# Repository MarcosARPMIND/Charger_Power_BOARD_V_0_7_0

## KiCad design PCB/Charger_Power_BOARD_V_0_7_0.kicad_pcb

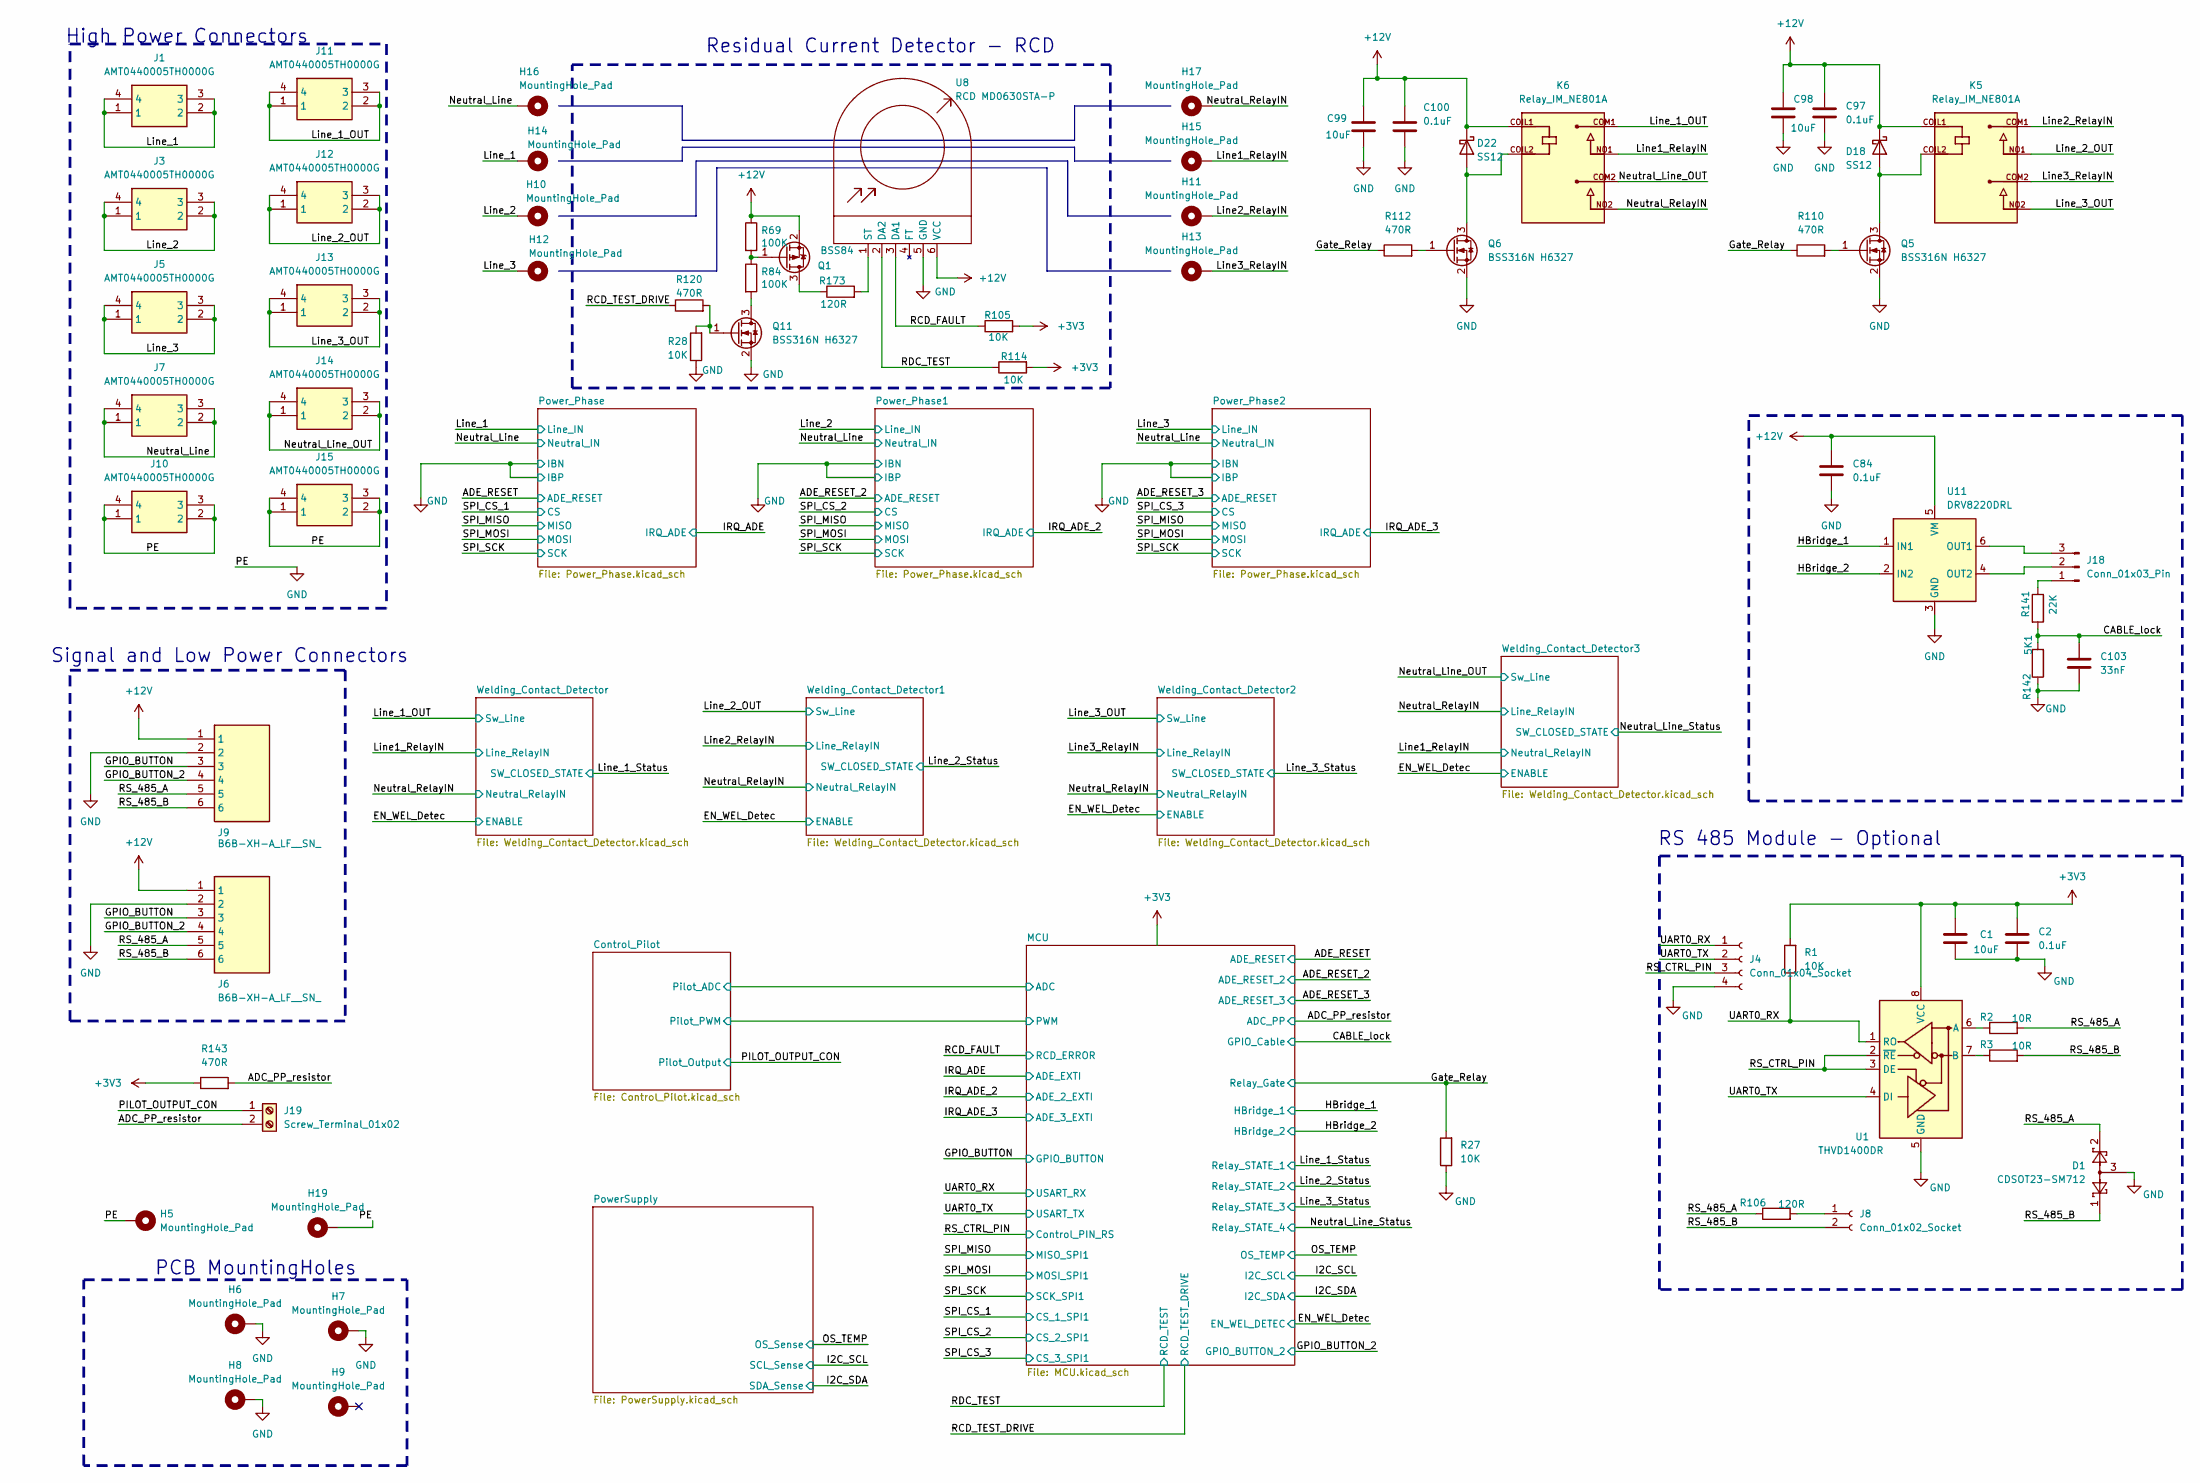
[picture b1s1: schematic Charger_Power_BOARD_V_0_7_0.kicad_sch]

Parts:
C1: 10uF; C_1206_3216Metric; MPN GMK316AB7106KL-TR
C2, C84, C97, C100: 0.1uF; C_0603_1608Metric; MPN CL10B104MB8NNNC
C98, C99: 10uF; C_1206_3216Metric
C103: 33nF; C_0603_1608Metric
D1: CDSOT23-SM712; SOT-23-3; MPN CDSOT23-SM712
D18, D22: SS12; D_SMA; MPN SS12-E3/61T
H5, H10, H11, H12, H13, H14, H15, H16, H17, H19: MountingHole_Pad; MountingHole_3.2mm_M3_DIN965_Pad_TopBottom
H6, H7, H8: MountingHole_Pad; MountingHole_5.3mm_M5_DIN965_Pad_TopBottom
H9: MountingHole_Pad; MountingHole_5.3mm_M5
J1, J3, J5, J7, J10, J11, J12, J13, J14, J15: AMT0440005TH0000G
J4: Conn_01x04_Socket; PinHeader_1x04_P2.54mm_Vertical
J6, J9: B6B-XH-A_LF__SN_; SHDR6W64P0X250_1X6_1740X575X700P
J8: Conn_01x02_Socket; PinHeader_1x02_P2.54mm_Vertical
J18: Conn_01x03_Pin; JST_VH_B3P-VH-FB-B_1x03_P3.96mm_Vertical
J19: Screw_Terminal_01x02; TerminalBlock_Phoenix_MKDS-3-2-5.08_1x02_P5.08mm_Horizontal
K5, K6: Relay_IM_NE801A
Q1: BSS84; SOT-23
Q5, Q6, Q11: BSS316N H6327; SOT-23; MPN BSS316N H6327
R1, R27, R28, R105, R114: 10K; R_0603_1608Metric; MPN RCS060310K0FKEA
R2, R3: 10R; R_0603_1608Metric; MPN 0603WAF100JT1E
R69, R84: 100K; R_0603_1608Metric
R106: 120R; R_0603_1608Metric; MPN CRCW0603120RFKEAC
R110, R112, R120, R143: 470R; R_0603_1608Metric
R141: 22K; R_0603_1608Metric
R142: 5K1; R_0603_1608Metric
R173: 120R; R_0603_1608Metric; MPN RE0603FRE07150RL
U1: THVD1400DR; SOIC127P600X175-8N
U8: RCD MD0630STA-P; RCD_MD0630STA_P
U11: DRV8220DRL; SOT-563

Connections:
+3V3: C1.2, C2.1, R1.2, R105.2, R114.2, R143.1, U1.8 (VCC); also elsewhere on the board
+12V: C84.1, C97.1, C98.1, C99.1, C100.1, D18.1 (K), D22.1 (K), J6.1, J9.1, K5.COIL1, K6.COIL1, Q1.2 (S), R69.1, U8.6 (VCC), U11.5 (VM); also elsewhere on the board
/ADC_PP_resistor: J19.2, R143.2; also elsewhere on the board
/CABLE_lock: C103.1, R141.2, R142.2; also elsewhere on the board
/GPIO_BUTTON: J6.3, J9.3; also elsewhere on the board
/GPIO_BUTTON_2: J6.4, J9.4; also elsewhere on the board
/Gate_Relay: R27.2, R110.1, R112.1; also elsewhere on the board
/HBridge_1: U11.1 (IN1); also elsewhere on the board
/HBridge_2: U11.2 (IN2); also elsewhere on the board
/Line1_RelayIN: H15.1 (1_1), K6.NO1; also elsewhere on the board
/Line2_RelayIN: H11.1 (1_1), K5.COM1; also elsewhere on the board
/Line3_RelayIN: H13.1 (1_1), K5.COM2; also elsewhere on the board
/Line_1: H14.1 (1_1), J1.1, J1.2, J1.3, J1.4; also elsewhere on the board
/Line_1_OUT: J11.1, J11.2, J11.3, J11.4, K6.COM1; also elsewhere on the board
/Line_2: H10.1 (1_1), J3.1, J3.2, J3.3, J3.4; also elsewhere on the board
/Line_2_OUT: J12.1, J12.2, J12.3, J12.4, K5.NO1; also elsewhere on the board
/Line_3: H12.1 (1_1), J5.1, J5.2, J5.3, J5.4; also elsewhere on the board
/Line_3_OUT: J13.1, J13.2, J13.3, J13.4, K5.NO2; also elsewhere on the board
/Neutral_Line: H16.1 (1_1), J7.1, J7.2, J7.3, J7.4; also elsewhere on the board
/Neutral_Line_OUT: J14.1, J14.2, J14.3, J14.4, K6.COM2; also elsewhere on the board
/Neutral_RelayIN: H17.1 (1_1), K6.NO2; also elsewhere on the board
/PILOT_OUTPUT_CON: J19.1; also elsewhere on the board
/RCD_FAULT: R105.1, U8.3 (DA1); also elsewhere on the board
/RCD_TEST_DRIVE: R120.1; also elsewhere on the board
/RDC_TEST: R114.1, U8.2 (DA2); also elsewhere on the board
/RS_485_A: D1.2, J6.5, J9.5, R2.2, R106.1
/RS_485_B: D1.1, J6.6, J8.2, J9.6, R3.2
/RS_CTRL_PIN: J4.3, U1.2 (~RE), U1.3 (DE); also elsewhere on the board
/UART0_RX: J4.1, R1.1, U1.1 (RO); also elsewhere on the board
/UART0_TX: J4.2, U1.4 (DI); also elsewhere on the board
GND: C1.1, C2.2, C84.2, C97.2, C98.2, C99.2, C100.2, C103.2, D1.3, H5.1 (1_1), H6.1 (1_1), H7.1 (1_1), H8.1 (1_1), H19.1 (1_1), J4.4, J6.2, J9.2, J10.1, J10.2, J10.3, J10.4, J15.1, J15.2, J15.3, J15.4, Q5.2 (S), Q6.2 (S), Q11.2 (S), R27.1, R28.1, R142.1, U1.5 (GND), U8.5 (GND), U11.3 (GND); also elsewhere on the board
unnamed: D18.2 (A), K5.COIL2, Q5.3 (D)
unnamed: D22.2 (A), K6.COIL2, Q6.3 (D)
unnamed: J8.1, R106.2
unnamed: J18.1, R141.1
unnamed: J18.2, U11.4 (OUT2)
unnamed: J18.3, U11.6 (OUT1)
unnamed: Q1.3 (D), R173.1
unnamed: Q1.1 (G), R69.2, R84.1
unnamed: Q5.1 (G), R110.2
unnamed: Q6.1 (G), R112.2
unnamed: Q11.3 (D), R84.2
unnamed: Q11.1 (G), R28.2, R120.2
unnamed: R2.1, U1.6 (A)
unnamed: R3.1, U1.7 (B)
unnamed: R173.2, U8.1 (ST)

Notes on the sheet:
PCB MountingHoles
Residual Current Detector - RCD
RS 485 Module - Optional
Signal and Low Power Connectors
High Power Connectors

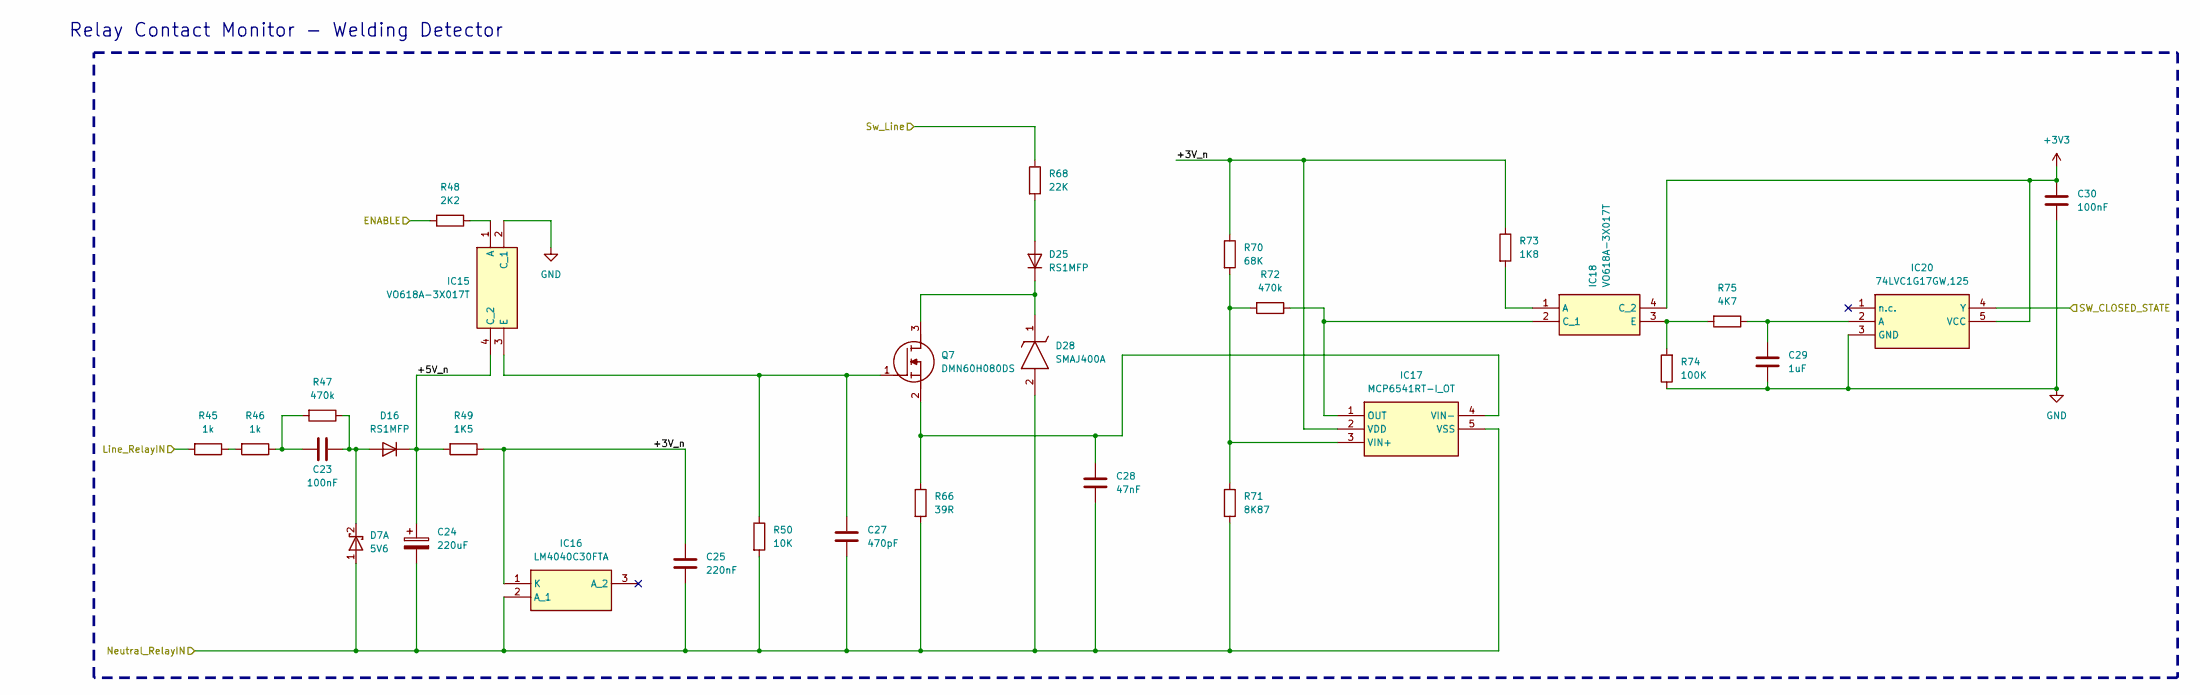
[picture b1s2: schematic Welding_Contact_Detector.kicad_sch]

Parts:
C23: 100nF; C_Rect_L18.0mm_W5.0mm_P15.00mm_FKS3_FKP3
C24: 220uF; CP_Radial_D8.0mm_P3.50mm
C25: 220nF; C_0603_1608Metric
C27: 470pF; C_0603_1608Metric
C28: 47nF; C_0603_1608Metric
C29: 1uF; C_0603_1608Metric
C30: 100nF; C_0603_1608Metric
D7: 5V6; D_SOD-123
D16, D25: RS1MFP; D_SOD-123
D28: SMAJ400A; DIOM5026X229N
IC15, IC18: VO618A-3X017T; SMD-4_OPTION_7
IC16: LM4040C30FTA; SOT-23-3
IC17: MCP6541RT-I_OT; SOT95P280X145-5N
IC20: 74LVC1G17GW,125; SOT65P212X110-5N
Q7: DMN60H080DS; SOT-23-3
R45, R46: 1k; R_1206_3216Metric
R47: 470k; R_1206_3216Metric
R48: 2K2; R_0603_1608Metric
R49: 1K5; R_0603_1608Metric
R50: 10K; R_0603_1608Metric
R66: 39R; R_0603_1608Metric
R68: 22K; R_Axial_DIN0411_L9.9mm_D3.6mm_P12.70mm_Horizontal
R70: 68K; R_0603_1608Metric
R71: 8K87; R_0603_1608Metric
R72: 470k; R_0603_1608Metric
R73: 1K8; R_0603_1608Metric
R74: 100K; R_0603_1608Metric
R75: 4K7; R_0603_1608Metric

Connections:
+3V3: C30.1, IC18.4 (C_2), IC20.5 (VCC); also elsewhere on the board
/EN_WEL_Detec: R48.2; also elsewhere on the board
/Line2_RelayIN: R45.2; also elsewhere on the board
/Line_2_OUT: R68.1; also elsewhere on the board
/Line_2_Status: IC20.4 (Y); also elsewhere on the board
/Neutral_RelayIN: C24.2, C25.2, C27.2, C28.2, D7.1 (A), D28.2 (A), IC16.2 (A_1), IC17.5 (VSS), R50.2, R66.2, R71.2; also elsewhere on the board
/Welding_Contact_Detector1/+3V_n: C25.1, IC16.1 (K), IC17.2 (VDD), R49.1, R70.1, R73.1
/Welding_Contact_Detector1/+5V_n: C24.1, D16.1 (K), IC15.4 (C_2), R49.2
GND: C29.2, C30.2, IC15.2 (C_1), IC20.3 (GND), R74.1; also elsewhere on the board
unnamed: C23.2, R46.1, R47.2
unnamed: C23.1, D7.2 (K), D16.2 (A), R47.1
unnamed: D25.2 (A), R68.2
unnamed: D25.1 (K), D28.1 (K), Q7.3 (D)
unnamed: IC15.1 (A), R48.1
unnamed: C27.1, IC15.3 (E), Q7.1 (G), R50.1
unnamed: IC17.1 (OUT), IC18.2 (C_1), R72.1
unnamed: IC17.3 (VIN+), R70.2, R71.1, R72.2
unnamed: C28.1, IC17.4 (VIN-), Q7.2 (S), R66.1
unnamed: IC18.1 (A), R73.2
unnamed: IC18.3 (E), R74.2, R75.2
unnamed: C29.1, IC20.2 (A), R75.1
unnamed: R45.1, R46.2

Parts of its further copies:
C26, C37, C61: 100nF; C_Rect_L18.0mm_W5.0mm_P15.00mm_FKS3_FKP3
C31, C38, C62: 220uF; CP_Radial_D8.0mm_P3.50mm
C32, C39, C63: 220nF; C_0603_1608Metric
C33, C40, C64: 470pF; C_0603_1608Metric
C34, C58, C65: 47nF; C_0603_1608Metric
C35, C59, C66: 1uF; C_0603_1608Metric
C36, C60, C67: 100nF; C_0603_1608Metric
D29, D49, D53: 5V6; D_SOD-123
D30, D31, D50, D51, D54, D55: RS1MFP; D_SOD-123
D48, D52, D56: SMAJ400A; DIOM5026X229N
IC21, IC24, IC26, IC46, IC48, IC51: VO618A-3X017T; SMD-4_OPTION_7
IC22, IC27, IC49: LM4040C30FTA; SOT-23-3
IC23, IC45, IC50: MCP6541RT-I_OT; SOT95P280X145-5N
IC25, IC47, IC52: 74LVC1G17GW,125; SOT65P212X110-5N
Q8, Q9, Q10: DMN60H080DS; SOT-23-3
R76, R77, R91, R92, R127, R128: 1k; R_1206_3216Metric
R78, R93, R129: 470k; R_1206_3216Metric
R79, R115, R130: 2K2; R_0603_1608Metric
R80, R116, R131: 1K5; R_0603_1608Metric
R81, R117, R132: 10K; R_0603_1608Metric
R82, R118, R133: 39R; R_0603_1608Metric
R83, R119, R134: 22K; R_Axial_DIN0411_L9.9mm_D3.6mm_P12.70mm_Horizontal
R85, R121, R136: 68K; R_0603_1608Metric
R86, R122, R137: 8K87; R_0603_1608Metric
R87, R123, R138: 470k; R_0603_1608Metric
R88, R124, R139: 1K8; R_0603_1608Metric
R89, R125, R140: 100K; R_0603_1608Metric
R90, R126, R215: 4K7; R_0603_1608Metric

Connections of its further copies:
+3V3: C36.1, C60.1, C67.1, IC24.4 (C_2), IC25.5 (VCC), IC46.4 (C_2), IC47.5 (VCC), IC51.4 (C_2), IC52.5 (VCC); also elsewhere on the board
/EN_WEL_Detec: R79.2, R115.2, R130.2; also elsewhere on the board
/Line1_RelayIN: C62.2, C63.2, C64.2, C65.2, D53.1 (A), D56.2 (A), IC49.2 (A_1), IC50.5 (VSS), R91.2, R132.2, R133.2, R137.2; also elsewhere on the board
/Line3_RelayIN: R76.2; also elsewhere on the board
/Line_1_OUT: R119.1; also elsewhere on the board
/Line_1_Status: IC47.4 (Y); also elsewhere on the board
/Line_3_OUT: R83.1; also elsewhere on the board
/Line_3_Status: IC25.4 (Y); also elsewhere on the board
/Neutral_Line_OUT: R134.1; also elsewhere on the board
/Neutral_Line_Status: IC52.4 (Y); also elsewhere on the board
/Neutral_RelayIN: C31.2, C32.2, C33.2, C34.2, C38.2, C39.2, C40.2, C58.2, D29.1 (A), D48.2 (A), D49.1 (A), D52.2 (A), IC22.2 (A_1), IC23.5 (VSS), IC27.2 (A_1), IC45.5 (VSS), R81.2, R82.2, R86.2, R117.2, R118.2, R122.2, R127.2; also elsewhere on the board
/Welding_Contact_Detector2/+3V_n: C32.1, IC22.1 (K), IC23.2 (VDD), R80.1, R85.1, R88.1
/Welding_Contact_Detector2/+5V_n: C31.1, D30.1 (K), IC21.4 (C_2), R80.2
/Welding_Contact_Detector3/+3V_n: C63.1, IC49.1 (K), IC50.2 (VDD), R131.1, R136.1, R139.1
/Welding_Contact_Detector3/+5V_n: C62.1, D54.1 (K), IC48.4 (C_2), R131.2
/Welding_Contact_Detector/+3V_n: C39.1, IC27.1 (K), IC45.2 (VDD), R116.1, R121.1, R124.1
/Welding_Contact_Detector/+5V_n: C38.1, D50.1 (K), IC26.4 (C_2), R116.2
GND: C35.2, C36.2, C59.2, C60.2, C66.2, C67.2, IC21.2 (C_1), IC25.3 (GND), IC26.2 (C_1), IC47.3 (GND), IC48.2 (C_1), IC52.3 (GND), R89.1, R125.1, R140.1; also elsewhere on the board
unnamed: C26.2, R77.1, R78.2
unnamed: C37.2, R92.1, R93.2
unnamed: C61.2, R128.1, R129.2
unnamed: C26.1, D29.2 (K), D30.2 (A), R78.1
unnamed: D31.2 (A), R83.2
unnamed: D31.1 (K), D48.1 (K), Q8.3 (D)
unnamed: C37.1, D49.2 (K), D50.2 (A), R93.1
unnamed: D51.2 (A), R119.2
unnamed: D51.1 (K), D52.1 (K), Q9.3 (D)
unnamed: C61.1, D53.2 (K), D54.2 (A), R129.1
unnamed: D55.2 (A), R134.2
unnamed: D55.1 (K), D56.1 (K), Q10.3 (D)
unnamed: IC21.1 (A), R79.1
unnamed: C33.1, IC21.3 (E), Q8.1 (G), R81.1
unnamed: IC23.1 (OUT), IC24.2 (C_1), R87.1
unnamed: IC23.3 (VIN+), R85.2, R86.1, R87.2
unnamed: C34.1, IC23.4 (VIN-), Q8.2 (S), R82.1
unnamed: IC24.1 (A), R88.2
unnamed: IC24.3 (E), R89.2, R90.2
unnamed: C35.1, IC25.2 (A), R90.1
unnamed: IC26.1 (A), R115.1
unnamed: C40.1, IC26.3 (E), Q9.1 (G), R117.1
unnamed: IC45.1 (OUT), IC46.2 (C_1), R123.1
unnamed: IC45.3 (VIN+), R121.2, R122.1, R123.2
unnamed: C58.1, IC45.4 (VIN-), Q9.2 (S), R118.1
unnamed: IC46.1 (A), R124.2
unnamed: IC46.3 (E), R125.2, R126.2
unnamed: C59.1, IC47.2 (A), R126.1
unnamed: IC48.1 (A), R130.1
unnamed: C64.1, IC48.3 (E), Q10.1 (G), R132.1
unnamed: IC50.1 (OUT), IC51.2 (C_1), R138.1
unnamed: IC50.3 (VIN+), R136.2, R137.1, R138.2
unnamed: C65.1, IC50.4 (VIN-), Q10.2 (S), R133.1
unnamed: IC51.1 (A), R139.2
unnamed: IC51.3 (E), R140.2, R215.2
unnamed: C66.1, IC52.2 (A), R215.1
unnamed: R76.1, R77.2
unnamed: R91.1, R92.2
unnamed: R127.1, R128.2

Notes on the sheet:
Relay Contact Monitor - Welding Detector

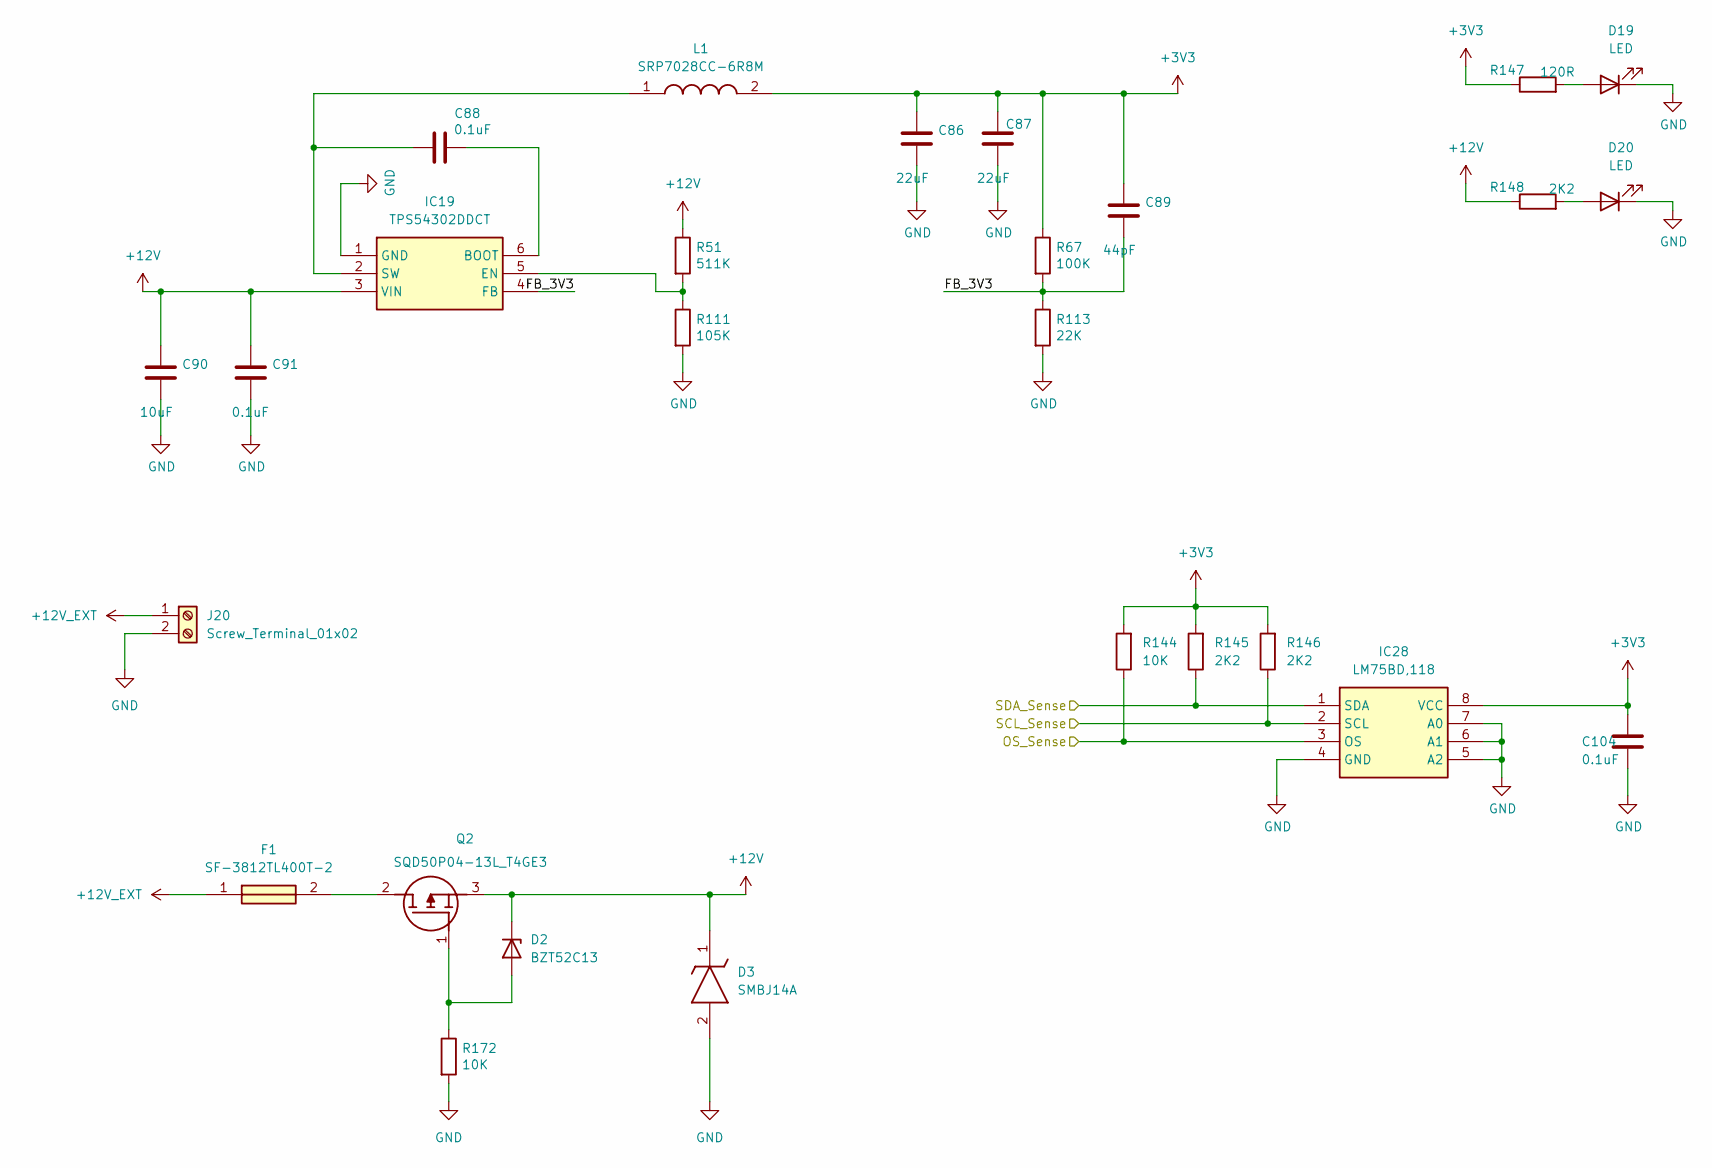
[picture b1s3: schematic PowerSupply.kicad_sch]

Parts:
C86, C87: 22uF; C_1206_3216Metric
C88, C91: 0.1uF; C_0603_1608Metric
C89: 44pF; C_0603_1608Metric
C90: 10uF; C_1206_3216Metric
C104: 0.1uF; C_0603_1608Metric; MPN CL10B104MB8NNNC
D2: BZT52C13; D_SOD-123
D3: SMBJ14A; DIOM5436X261N; Manufacturer_Part_Number SMBJ14A
D19, D20: LED; LED_0603_1608Metric
F1: SF-3812TL400T-2; SF3812TL400T2; Mouser Part Number 652-SF-3812TL400T-2
IC19: TPS54302DDCT; SOT95P280X110-6N
IC28: LM75BD,118; SOIC127P600X175-8N
J20: Screw_Terminal_01x02; TerminalBlock_Phoenix_MKDS-3-2-5.08_1x02_P5.08mm_Horizontal
L1: SRP7028CC-6R8M; INDPM7366X300N
Q2: SQD50P04-13L_T4GE3; SQD50P0413L_T4GE3; Mouser Part Number 78-SQD50P04-13LT4GE3
R51: 511K; R_0603_1608Metric
R67: 100K; R_0603_1608Metric
R111: 105K; R_0603_1608Metric
R113: 22K; R_0603_1608Metric
R144, R172: 10K; R_0603_1608Metric; MPN RCS060310K0FKEA
R145, R146: 2K2; R_0603_1608Metric; MPN RCS060310K0FKEA
R147: 120R; R_0603_1608Metric; MPN CRCW0603120RFKEAC
R148: 2K2; R_0603_1608Metric; MPN AC0603FR-072K2L

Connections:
+3V3: C86.1, C87.1, C89.1, C104.1, IC28.8 (VCC), L1.2, R67.1, R144.2, R145.2, R146.2, R147.1; also elsewhere on the board
+12V: C90.1, C91.1, D2.1 (K), D3.1 (K), IC19.3 (VIN), Q2.3 (S), R51.1, R148.1; also elsewhere on the board
+12V_EXT: F1.1, J20.1
/I2C_SCL: IC28.2 (SCL), R146.1; also elsewhere on the board
/I2C_SDA: IC28.1 (SDA), R145.1; also elsewhere on the board
/OS_TEMP: IC28.3 (OS), R144.1; also elsewhere on the board
/PowerSupply/FB_3V3: C89.2, IC19.4 (FB), R67.2, R113.1
GND: C86.2, C87.2, C90.2, C91.2, C104.2, D3.2 (A), D19.1 (K), D20.1 (K), IC19.1 (GND), IC28.4 (GND), IC28.5 (A2), IC28.6 (A1), IC28.7 (A0), J20.2, R111.2, R113.2, R172.2; also elsewhere on the board
unnamed: D2.2 (A), Q2.1 (G), R172.1
unnamed: D19.2 (A), R147.2
unnamed: D20.2 (A), R148.2
unnamed: C88.2, IC19.6 (BOOT)
unnamed: IC19.5 (EN), R51.2, R111.1
unnamed: C88.1, IC19.2 (SW), L1.1
unnamed: F1.2, Q2.2 (D)

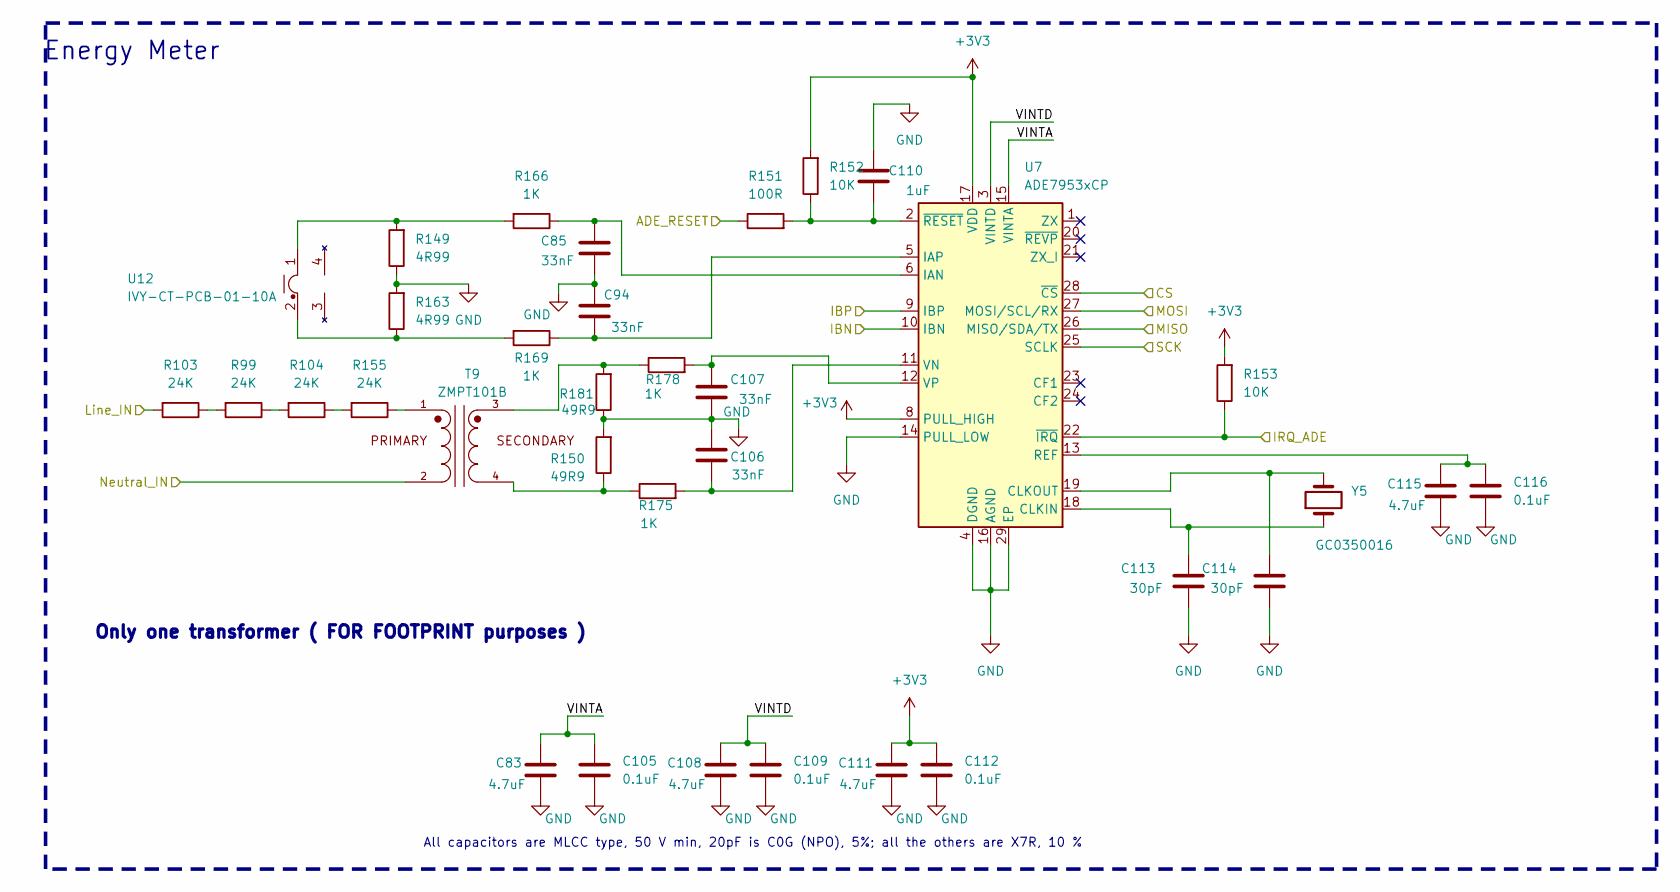
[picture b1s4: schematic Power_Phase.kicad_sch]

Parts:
C83, C108, C111, C115: 4.7uF; C_0805_2012Metric; MPN GRM21BZ7YA475ME15L
C85, C94, C106, C107: 33nF; C_0603_1608Metric_Pad1.08x0.95mm_HandSolder; MPN 0603B333J500CT
C105, C109, C112, C116: 0.1uF; C_0603_1608Metric; MPN CL10B104MB8NNNC
C110: 1uF; C_1206_3216Metric; MPN CL10B105KB8NQNC
C113, C114: 30pF; C_0603_1608Metric_Pad1.08x0.95mm_HandSolder; MPN CML0603C0G300JT50V
R99, R103, R104, R155: 24K; R_1206_3216Metric; MPN ESR18EZPF2402
R149, R163: 4R99; R_0603_1608Metric; MPN CRCW06034K99FKEAC
R150, R181: 49R9; R_0603_1608Metric; MPN CRCW0603100RJNEA
R151: 100R; R_0603_1608Metric; MPN CRCW0603100RJNEA
R152, R153: 10K; R_0603_1608Metric; MPN RCS060310K0FKEA
R166, R169, R175, R178: 1K; R_0603_1608Metric; MPN CRCW060336R0FKEA
T9: ZMPT101B; XFMR_ZMPT101B
U7: ADE7953xCP; LFCSP-28-1EP_5x5mm_P0.5mm_EP3.14x3.14mm_ThermalVias_MigCOM; MPN ADE7953ACPZ
U12: IVY-CT-PCB-01-10A; CT_IVY_01_10A
Y5: GC0350016; Crystal_SMD_HC49-SD; MPN GC0350016

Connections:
+3V3: C111.2, C112.1, R152.2, R153.2, U7.7 (PULL_HIGH), U7.8 (PULL_HIGH), U7.17 (VDD); also elsewhere on the board
/ADE_RESET_2: R151.1; also elsewhere on the board
/IRQ_ADE_2: R153.1, U7.22 (~IRQ); also elsewhere on the board
/Line_2: R103.2; also elsewhere on the board
/Neutral_Line: T9.2; also elsewhere on the board
/Power_Phase1/VINTA: C83.2, C105.1, U7.15 (VINTA)
/Power_Phase1/VINTD: C108.2, C109.1, U7.3 (VINTD)
/SPI_CS_2: U7.28 (~CS); also elsewhere on the board
/SPI_MISO: U7.26 (MISO/SDA/TX); also elsewhere on the board
/SPI_MOSI: U7.27 (MOSI/SCL/RX); also elsewhere on the board
/SPI_SCK: U7.25 (SCLK); also elsewhere on the board
GND: C83.1, C85.1, C94.2, C105.2, C106.2, C107.1, C108.1, C109.2, C110.2, C111.1, C112.2, C113.1, C114.1, C115.1, C116.2, R149.1, R150.2, R163.2, R181.1, U7.4 (DGND), U7.9 (IBP), U7.10 (IBN), U7.14 (PULL_LOW), U7.16 (AGND), U7.29 (EP); also elsewhere on the board
unnamed: R99.2, R103.1
unnamed: R104.1, R155.2
unnamed: R99.1, R104.2
unnamed: R149.2, R166.2, U12.1
unnamed: R150.1, R175.1, T9.4
unnamed: R155.1, T9.1
unnamed: R163.1, R169.2, U12.2
unnamed: R178.1, R181.2, T9.3
unnamed: C113.2, U7.18 (CLKIN), Y5.1
unnamed: C114.2, U7.19 (CLKOUT), Y5.2
unnamed: C85.2, R166.1, U7.6 (IAN)
unnamed: C94.1, R169.1, U7.5 (IAP)
unnamed: C115.2, C116.1, U7.13 (REF)
unnamed: C106.1, R175.2, U7.11 (VN)
unnamed: C107.2, R178.2, U7.12 (VP)
unnamed: C110.1, R151.2, R152.1, U7.2 (~RESET)

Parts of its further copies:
C70, C123: 1uF; C_1206_3216Metric; MPN CL10B105KB8NQNC
C71, C77, C79, C81, C117, C121, C124, C128: 4.7uF; C_0805_2012Metric; MPN GRM21BZ7YA475ME15L
C72, C78, C80, C82, C118, C122, C125, C129: 0.1uF; C_0603_1608Metric; MPN CL10B104MB8NNNC
C73, C74, C92, C93, C95, C96, C119, C120: 33nF; C_0603_1608Metric_Pad1.08x0.95mm_HandSolder; MPN 0603B333J500CT
C75, C76, C126, C127: 30pF; C_0603_1608Metric_Pad1.08x0.95mm_HandSolder; MPN CML0603C0G300JT50V
R94, R97, R161, R162: 10K; R_0603_1608Metric; MPN RCS060310K0FKEA
R95, R160: 100R; R_0603_1608Metric; MPN CRCW0603100RJNEA
R96, R158, R164, R165: 4R99; R_0603_1608Metric; MPN CRCW06034K99FKEAC
R98, R100, R101, R107, R108, R154, R156, R157: 24K; R_1206_3216Metric; MPN ESR18EZPF2402
R102, R159, R182, R183: 49R9; R_0603_1608Metric; MPN CRCW0603100RJNEA
R167, R168, R170, R171, R176, R177, R179, R180: 1K; R_0603_1608Metric; MPN CRCW060336R0FKEA
T7, T11: ZMPT101B; XFMR_ZMPT101B
U6, U9: ADE7953xCP; LFCSP-28-1EP_5x5mm_P0.5mm_EP3.14x3.14mm_ThermalVias_MigCOM; MPN ADE7953ACPZ
U10, U13: IVY-CT-PCB-01-10A; CT_IVY_01_10A
Y4, Y6: GC0350016; Crystal_SMD_HC49-SD; MPN GC0350016

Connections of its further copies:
+3V3: C81.2, C82.1, C124.2, C125.1, R94.2, R97.2, R161.2, R162.2, U6.7 (PULL_HIGH), U6.8 (PULL_HIGH), U6.17 (VDD), U9.7 (PULL_HIGH), U9.8 (PULL_HIGH), U9.17 (VDD); also elsewhere on the board
/ADE_RESET: R95.1; also elsewhere on the board
/ADE_RESET_3: R160.1; also elsewhere on the board
/IRQ_ADE: R97.1, U6.22 (~IRQ); also elsewhere on the board
/IRQ_ADE_3: R162.1, U9.22 (~IRQ); also elsewhere on the board
/Line_1: R98.2; also elsewhere on the board
/Line_3: R154.2; also elsewhere on the board
/Neutral_Line: T7.2, T11.2; also elsewhere on the board
/Power_Phase2/VINTA: C117.2, C118.1, U9.15 (VINTA)
/Power_Phase2/VINTD: C121.2, C122.1, U9.3 (VINTD)
/Power_Phase/VINTA: C77.2, C78.1, U6.15 (VINTA)
/Power_Phase/VINTD: C79.2, C80.1, U6.3 (VINTD)
/SPI_CS_1: U6.28 (~CS); also elsewhere on the board
/SPI_CS_3: U9.28 (~CS); also elsewhere on the board
/SPI_MISO: U6.26 (MISO/SDA/TX), U9.26 (MISO/SDA/TX); also elsewhere on the board
/SPI_MOSI: U6.27 (MOSI/SCL/RX), U9.27 (MOSI/SCL/RX); also elsewhere on the board
/SPI_SCK: U6.25 (SCLK), U9.25 (SCLK); also elsewhere on the board
GND: C70.2, C71.1, C72.2, C73.2, C74.1, C75.1, C76.1, C77.1, C78.2, C79.1, C80.2, C81.1, C82.2, C92.1, C93.1, C95.2, C96.2, C117.1, C118.2, C119.2, C120.1, C121.1, C122.2, C123.2, C124.1, C125.2, C126.1, C127.1, C128.1, C129.2, R96.1, R102.2, R158.1, R159.2, R164.2, R165.2, R182.1, R183.1, U6.4 (DGND), U6.9 (IBP), U6.10 (IBN), U6.14 (PULL_LOW), U6.16 (AGND), U6.29 (EP), U9.4 (DGND), U9.9 (IBP), U9.10 (IBN), U9.14 (PULL_LOW), U9.16 (AGND), U9.29 (EP); also elsewhere on the board
unnamed: R100.1, R107.2
unnamed: R100.2, R154.1
unnamed: R101.1, R108.2
unnamed: R98.1, R101.2
unnamed: R102.1, R177.1, T7.4
unnamed: R107.1, R156.2
unnamed: R108.1, R157.2
unnamed: R156.1, T11.1
unnamed: R157.1, T7.1
unnamed: R158.2, R167.2, U13.1
unnamed: R159.1, R176.1, T11.4
unnamed: R164.1, R170.2, U13.2
unnamed: R165.1, R171.2, U10.2
unnamed: R96.2, R168.2, U10.1
unnamed: R179.1, R182.2, T11.3
unnamed: R180.1, R183.2, T7.3
unnamed: C75.2, U6.18 (CLKIN), Y4.1
unnamed: C76.2, U6.19 (CLKOUT), Y4.2
unnamed: C93.2, R168.1, U6.6 (IAN)
unnamed: C96.1, R171.1, U6.5 (IAP)
unnamed: C71.2, C72.1, U6.13 (REF)
unnamed: C73.1, R177.2, U6.11 (VN)
unnamed: C74.2, R180.2, U6.12 (VP)
unnamed: C70.1, R94.1, R95.2, U6.2 (~RESET)
unnamed: C126.2, U9.18 (CLKIN), Y6.1
unnamed: C127.2, U9.19 (CLKOUT), Y6.2
unnamed: C92.2, R167.1, U9.6 (IAN)
unnamed: C95.1, R170.1, U9.5 (IAP)
unnamed: C128.2, C129.1, U9.13 (REF)
unnamed: C119.1, R176.2, U9.11 (VN)
unnamed: C120.2, R179.2, U9.12 (VP)
unnamed: C123.1, R160.2, R161.1, U9.2 (~RESET)

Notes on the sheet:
All capacitors are MLCC type, 50 V min, 20pF is C0G (NPO), 5%; all the others are X7R, 10 %
Energy Meter
Only one transformer ( FOR FOOTPRINT purposes )
